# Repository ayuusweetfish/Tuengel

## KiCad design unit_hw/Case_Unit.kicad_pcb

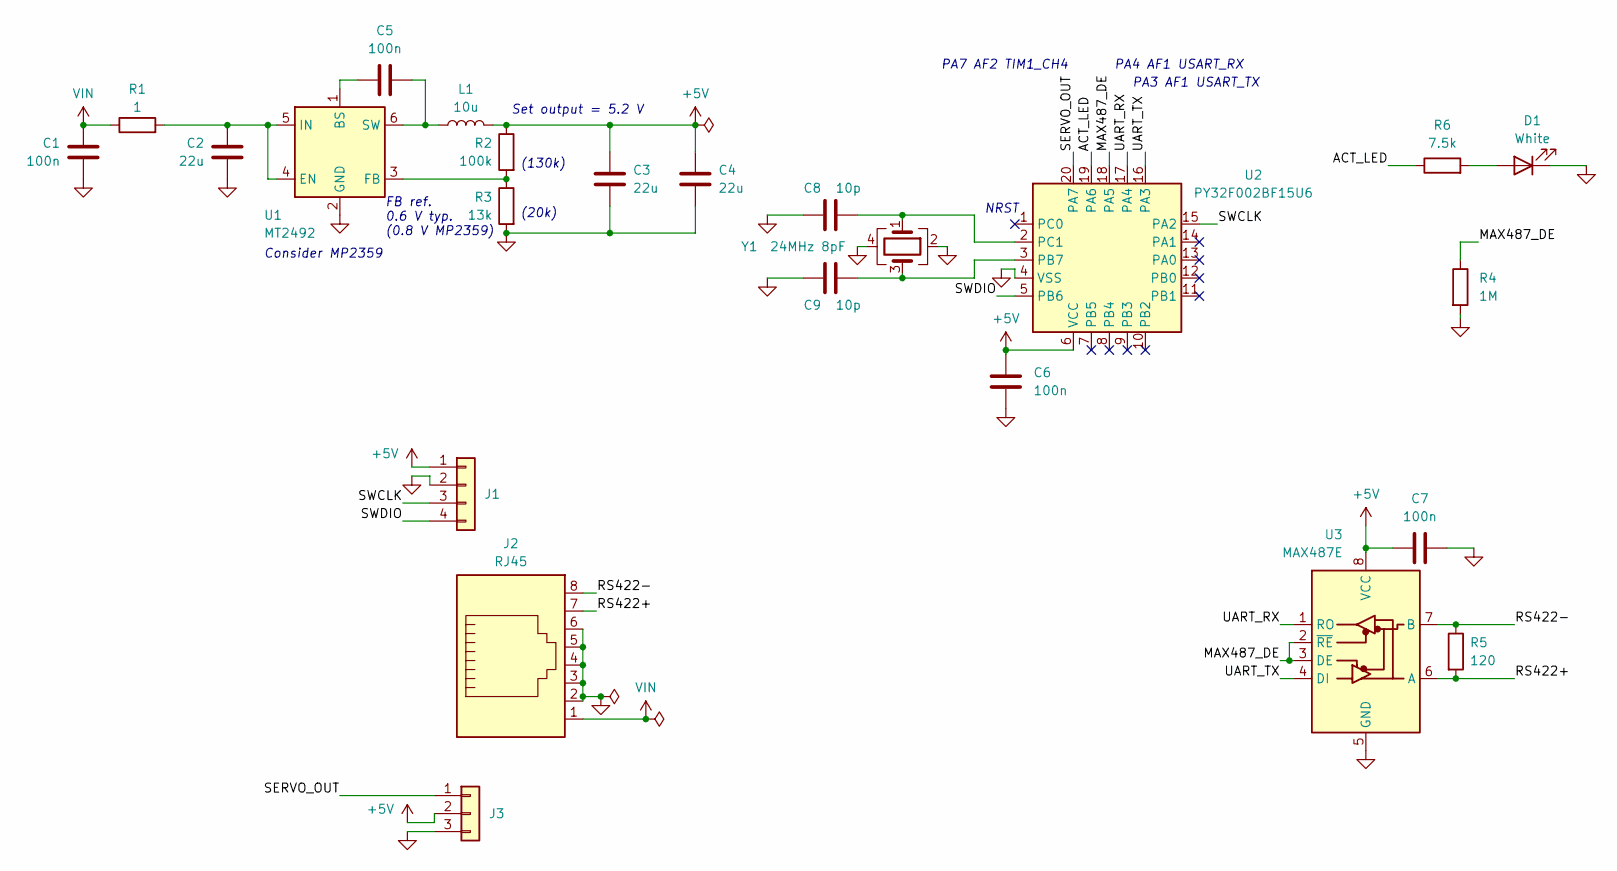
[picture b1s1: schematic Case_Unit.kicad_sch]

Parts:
C1, C5, C6, C7: 100n; C_0402_1005Metric
C2, C3, C4: 22u; C_0603_1608Metric
C8, C9: 10p; C_0402_1005Metric
D1: White; LED_0603_1608Metric
J1: Conn_01x04; TestPoints_1x04_P2.0
J2: RJ45; RJ45_OST_PJ012-8P8CX_Vertical
J3: Conn_01x03; PinHeader_1x03_P2.54mm_Vertical
L1: 10u; L_Changjiang_FNR5030S
R1: 1; R_0402_1005Metric
R2: 100k; R_0402_1005Metric
R3: 13k; R_0402_1005Metric
R4: 1M; R_0402_1005Metric
R5: 120; R_0402_1005Metric
R6: 7.5k; R_0402_1005Metric
U1: MT2492; SOT-23-6; Manufacturer_Part_Number MT2492
U2: PY32F002BF15U6; QFN-20-1EP_3x3mm_P0.4mm_EP1.65x1.65mm
U3: MAX487E; SOIC-8_3.9x4.9mm_P1.27mm
Y1: 24MHz 8pF; Crystal_SMD_2016-4Pin_2.0x1.6mm

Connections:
+5V: C3.1, C4.1, C6.1, C7.1, J1.1, J3.2, L1.2, R2.1, U2.6 (VCC), U3.8 (VCC)
/ACT_LED: R6.1, U2.19 (PA6)
/MAX487_DE: R4.1, U2.18 (PA5), U3.2 (~RE), U3.3 (DE)
/RS422+: J2.7, R5.2, U3.6 (A)
/RS422-: J2.8, R5.1, U3.7 (B)
/SERVO_OUT: J3.1, U2.20 (PA7)
/SWCLK: J1.3, U2.15 (PA2)
/SWDIO: J1.4, U2.5 (PB6)
/UART_RX: U2.17 (PA4), U3.1 (RO)
/UART_TX: U2.16 (PA3), U3.4 (DI)
GND: C1.2, C2.2, C3.2, C4.2, C6.2, C7.2, C8.1, C9.1, D1.1 (K), J1.2, J2.2, J2.3, J2.4, J2.5, J2.6, J3.3, R3.2, R4.2, U1.2 (GND), U2.4 (VSS), U2.21 (PAD), U3.5 (GND), Y1.2, Y1.4
unnamed: D1.2 (A), R6.2
unnamed: C5.1, U1.1 (BS)
unnamed: C2.1, R1.2, U1.4 (EN), U1.5 (IN)
unnamed: R2.2, R3.1, U1.3 (FB)
unnamed: C5.2, L1.1, U1.6 (SW)
unnamed: C9.2, U2.3 (PB7), Y1.3
unnamed: C8.2, U2.2 (PC1), Y1.1
VIN: C1.1, J2.1, R1.1

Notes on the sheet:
PA4 AF1 USART_RX
Consider MP2359
(130k)
NRST
PA3 AF1 USART_TX
FB ref. 0.6 V typ. (0.8 V MP2359)
(20k)
PA7 AF2 TIM1_CH4
Set output = 5.2 V

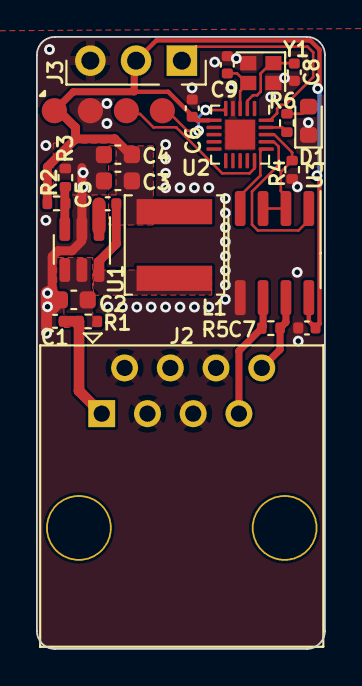
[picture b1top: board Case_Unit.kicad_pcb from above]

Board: 2 copper layers, 16.0 x 34.0 mm, 24 parts (0 on the bottom side), 19 nets.

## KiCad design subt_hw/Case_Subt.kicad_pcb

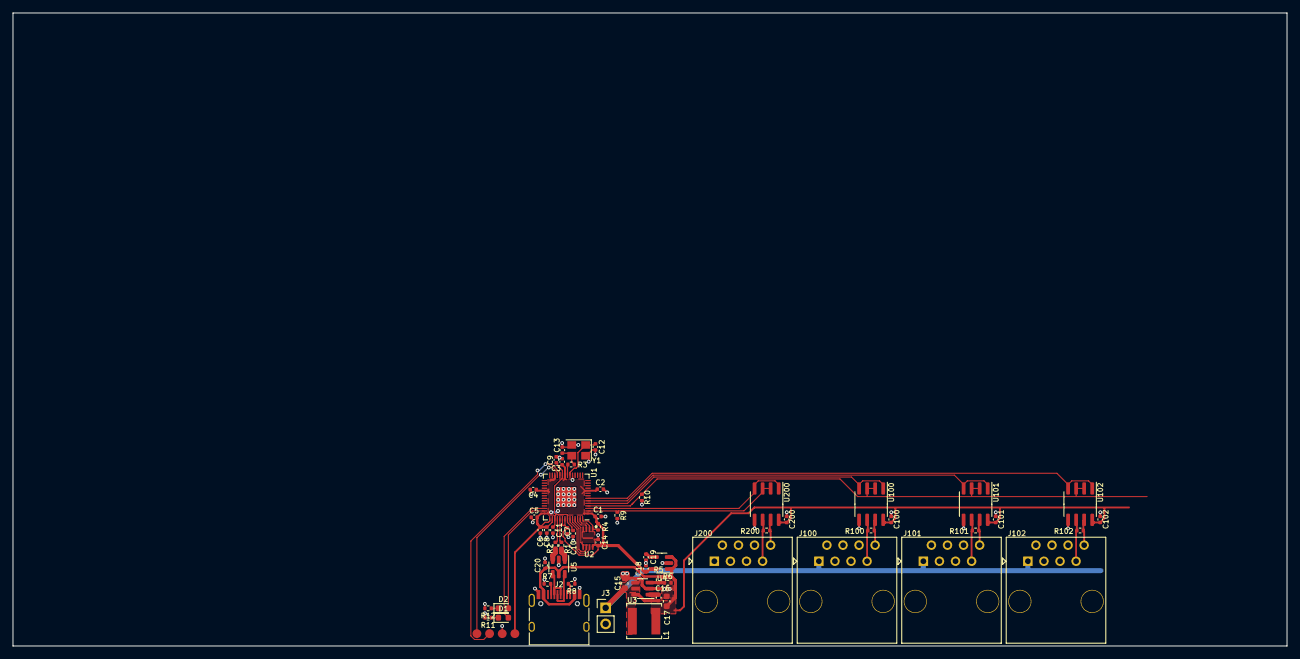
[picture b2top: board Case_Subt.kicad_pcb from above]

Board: 2 copper layers, 201.3 x 100.0 mm, 60 parts (0 on the bottom side), 46 nets.

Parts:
C1, C2, C3, C4, C5, C6, C7, C9, C10, C14, C20, C100, C101, C102, C200: 100n; C_0402_1005Metric
C8, C11: 1u; C_0402_1005Metric
C12, C13: 27p; C_0402_1005Metric
C15, C17: 22u; C_0603_1608Metric
C16: 22n; C_0402_1005Metric
C18: 4.7u; C_0402_1005Metric
C19: 10n; C_0402_1005Metric
D1: Pink; LED_0603_1608Metric
D2: Violet; LED_0603_1608Metric
J1: P2.00 01x04; TestPoints_1x04_P2.0
J2: USB_C_Receptacle_USB2.0_14P; USB_C_Receptacle_HRO_TYPE-C-31-M-12
J3: Conn_01x02; PinHeader_1x02_P2.54mm_Vertical
J100, J101, J102, J200: RJ45; RJ45_OST_PJ012-8P8CX_Vertical
L1: 10u; L_Changjiang_FNR5030S
R1, R2: 22; R_0402_1005Metric
R3: 1k TBD; R_0402_1005Metric
R4, R5: 100k; R_0402_1005Metric
R6: 22k; R_0402_1005Metric
R7, R8: 5.1k; R_0402_1005Metric
R9, R10: 1M; R_0402_1005Metric
R11, R12: 7.5k; R_0402_1005Metric
R100, R101, R102, R200: 120; R_0402_1005Metric
U1: RP2040; QFN-56-1EP_7x7mm_P0.4mm_EP3.2x3.2mm
U2: W25Q16JVUXIQ; SON50P300X200X60-9N
U3: MT2492; SOT-23-6
U4: SPX3819M5-L-3-3; SOT-23-5
U5: USBLC6-2SC6; SOT-23-6
U100, U101, U102, U200: MAX487E; SOIC-8_3.9x4.9mm_P1.27mm
Y1: 12MHz; Crystal_SMD_3225-4Pin_3.2x2.5mm

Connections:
+3V3: C1.1, C2.1, C3.1, C4.1, C5.1, C6.1, C7.1, C8.1, C14.1, C18.1, J1.1, R4.2, U1.1 (IOVDD), U1.10 (IOVDD), U1.22 (IOVDD), U1.26 (RUN), U1.33 (IOVDD), U1.42 (IOVDD), U1.43 (ADC_AVDD), U1.44 (VREG_IN), U1.48 (USB_VDD), U1.49 (IOVDD), U2.8 (VCC), U4.5 (OUT)
+5V: C17.1, C20.1, C100.1, C101.1, C102.1, C200.1, J2.A4 (VBUS), J2.A9 (VBUS), J2.B4 (VBUS), J2.B9 (VBUS), L1.2, R5.1, U4.1 (IN), U4.3 (EN), U5.5 (VBUS), U100.8 (VCC), U101.8 (VCC), U102.8 (VCC), U200.8 (VCC)
/ACT1: D1.2 (A), U1.40 (GPIO28_ADC2)
/ACT2: D2.2 (A), U1.41 (GPIO29_ADC3)
/DATA_00: U1.5 (GPIO3), U100.1 (RO), U100.4 (DI)
/DATA_01: U1.6 (GPIO4), U101.1 (RO), U101.4 (DI)
/DATA_02: U1.7 (GPIO5), U102.1 (RO), U102.4 (DI)
/DATA_IN: U1.3 (GPIO1), U200.1 (RO), U200.4 (DI)
/DE_ALL: R10.1, U1.4 (GPIO2), U100.2 (~RE), U100.3 (DE), U101.2 (~RE), U101.3 (DE), U102.2 (~RE), U102.3 (DE)
/DE_IN: R9.1, U1.2 (GPIO0), U200.2 (~RE), U200.3 (DE)
/FLASH_CS: R4.1, U1.56 (QSPI_SS), U2.1 (~CS)
/FLASH_D0: U1.53 (QSPI_SD0), U2.5 (DI_(IO0))
/FLASH_D1: U1.55 (QSPI_SD1), U2.2 (DO_(IO1))
/FLASH_D2: U1.54 (QSPI_SD2), U2.3 (~WP_(IO2))
/FLASH_D3: U1.51 (QSPI_SD3), U2.7 (~HOLD_OR_RESET_(IO3))
/FLASH_SCK: U1.52 (QSPI_SCLK), U2.6 (CLK)
/In_Conn/DATA+: J200.7, R200.2, U200.6 (A)
/In_Conn/DATA-: J200.8, R200.1, U200.7 (B)
/Out_00/DATA+: J100.7, R100.2, U100.6 (A)
/Out_00/DATA-: J100.8, R100.1, U100.7 (B)
/Out_01/DATA+: J101.7, R101.2, U101.6 (A)
/Out_01/DATA-: J101.8, R101.1, U101.7 (B)
/Out_02/DATA+: J102.7, R102.2, U102.6 (A)
/Out_02/DATA-: J102.8, R102.1, U102.7 (B)
/SWCLK: J1.3, U1.24 (SWCLK)
/SWDIO: J1.4, U1.25 (SWD)
/USB_D+: R1.1, U5.1 (I/O1)
/USB_D-: R2.1, U5.3 (I/O2)
/USB_RAW_D+: J2.A6 (D+), J2.B6 (D+), U5.6 (I/O1)
/USB_RAW_D-: J2.A7 (D-), J2.B7 (D-), U5.4 (I/O2)
GND: C1.2, C2.2, C3.2, C4.2, C5.2, C6.2, C7.2, C8.2, C9.2, C10.2, C11.2, C12.1, C13.1, C14.2, C15.2, C17.2, C18.2, C19.2, C20.2, C100.2, C101.2, C102.2, C200.2, J1.2, J2.A1 (GND), J2.A12 (GND), J2.B1 (GND), J2.B12 (GND), J3.2, J100.2, J100.3, J100.4, J100.5, J100.6, J101.2, J101.3, J101.4, J101.5, J101.6, J102.2, J102.3, J102.4, J102.5, J102.6, J200.2, J200.3, J200.4, J200.5, J200.6, R6.2, R7.1, R8.1, R9.2, R10.2, R11.2, R12.2, U1.19 (TESTEN), U1.57 (GND), U2.4 (GND), U2.9 (EP), U3.2 (GND), U4.2 (GND), U5.2 (GND), U100.5 (GND), U101.5 (GND), U102.5 (GND), U200.5 (GND), Y1.2, Y1.4
unnamed: C13.2, R3.1, Y1.3
unnamed: D1.1 (K), R11.1
unnamed: D2.1 (K), R12.1
unnamed: J2.A5 (CC1), R7.2
unnamed: J2.B5 (CC2), R8.2
unnamed: R2.2, U1.46 (USB_DM)
unnamed: R1.2, U1.47 (USB_DP)
unnamed: C12.2, U1.20 (XIN), Y1.1
unnamed: R3.2, U1.21 (XOUT)
unnamed: C16.1, U3.1 (BS)
unnamed: R5.2, R6.1, U3.3 (FB)
unnamed: C16.2, L1.1, U3.6 (SW)
unnamed: C19.1, U4.4 (BP)
VCORE: C9.1, C10.1, C11.1, U1.23 (DVDD), U1.45 (VREG_VOUT), U1.50 (DVDD)
VIN: C15.1, J3.1, J100.1, J101.1, J102.1, U3.4 (EN), U3.5 (IN)

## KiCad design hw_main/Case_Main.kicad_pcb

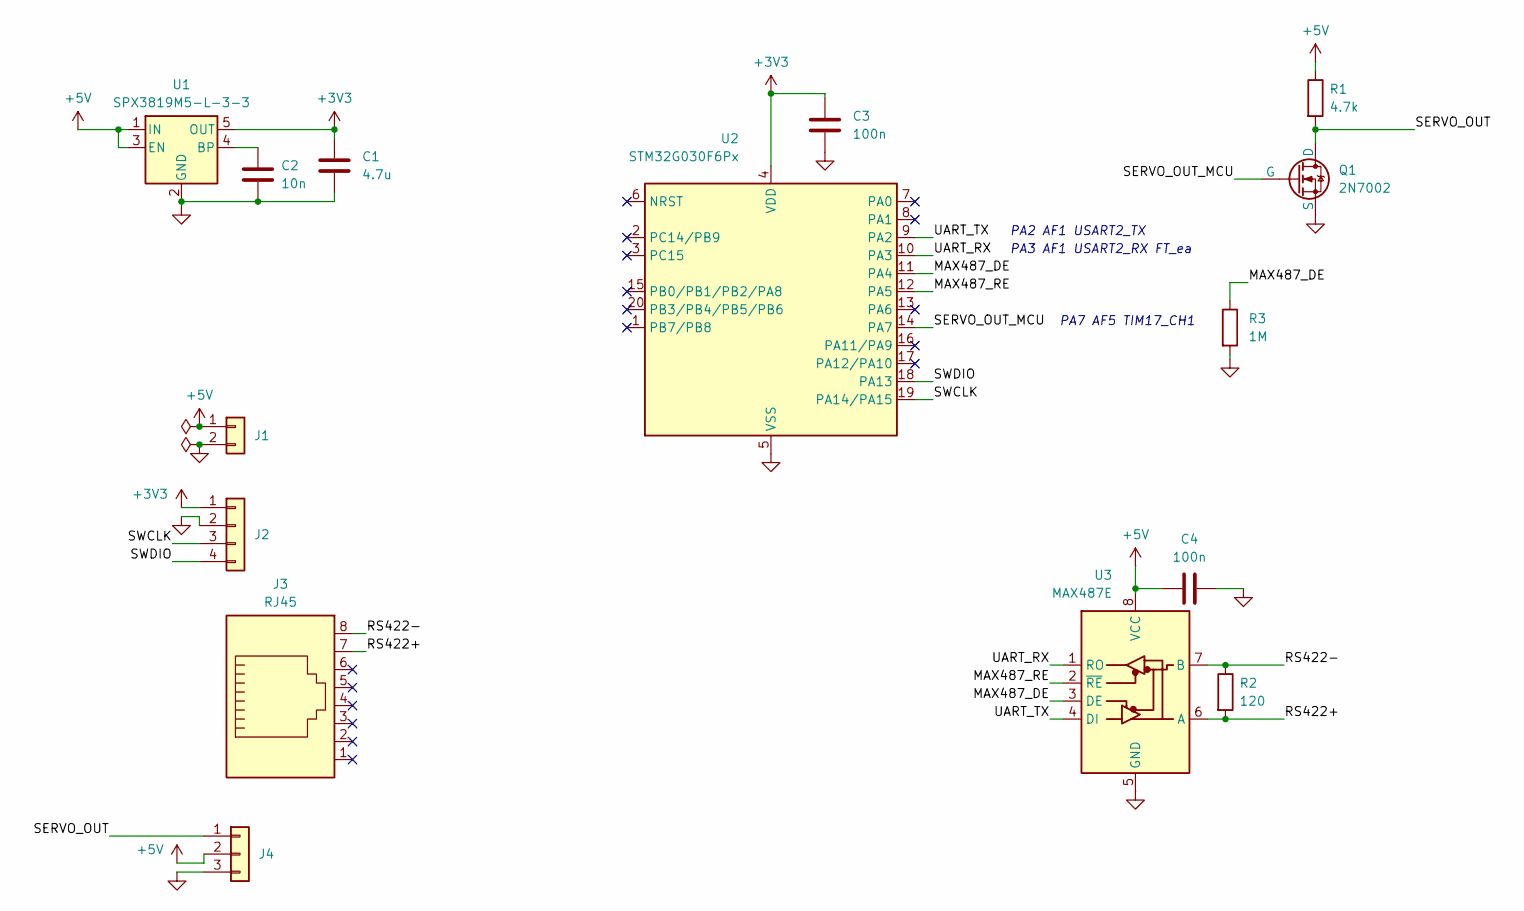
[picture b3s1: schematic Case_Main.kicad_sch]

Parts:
C1: 4.7u; C_0402_1005Metric
C2: 10n; C_0402_1005Metric
C3, C4: 100n; C_0402_1005Metric
J1: Conn_01x02; PinHeader_1x02_P2.54mm_Vertical
J2: Conn_01x04; TestPoints_1x04_P2.0
J3: RJ45; RJ45_OST_PJ012-8P8CX_Vertical
J4: Conn_01x03; PinHeader_1x03_P2.54mm_Vertical
Q1: 2N7002; SOT-23
R1: 4.7k; R_0402_1005Metric
R2: 120; R_0402_1005Metric
R3: 1M; R_0402_1005Metric
U1: SPX3819M5-L-3-3; SOT-23-5
U2: STM32G030F6Px; TSSOP-20_4.4x6.5mm_P0.65mm
U3: MAX487E; SOIC-8_3.9x4.9mm_P1.27mm

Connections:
+3V3: C1.1, C3.1, J2.1, U1.5 (OUT), U2.4 (VDD)
+5V: C4.1, J1.1, J4.2, R1.1, U1.1 (IN), U1.3 (EN), U3.8 (VCC)
/MAX487_DE: R3.1, U2.11 (PA4), U3.3 (DE)
/MAX487_RE: U2.12 (PA5), U3.2 (~RE)
/RS422+: J3.7, R2.2, U3.6 (A)
/RS422-: J3.8, R2.1, U3.7 (B)
/SERVO_OUT: J4.1, Q1.3 (D), R1.2
/SERVO_OUT_MCU: Q1.1 (G), U2.14 (PA7)
/SWCLK: J2.3, U2.19 (PA14/PA15)
/SWDIO: J2.4, U2.18 (PA13)
/UART_RX: U2.10 (PA3), U3.1 (RO)
/UART_TX: U2.9 (PA2), U3.4 (DI)
GND: C1.2, C2.2, C3.2, C4.2, J1.2, J2.2, J4.3, Q1.2 (S), R3.2, U1.2 (GND), U2.5 (VSS), U3.5 (GND)
unnamed: C2.1, U1.4 (BP)

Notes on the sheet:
PA3 AF1 USART2_RX FT_ea
PA2 AF1 USART2_TX
PA7 AF5 TIM17_CH1

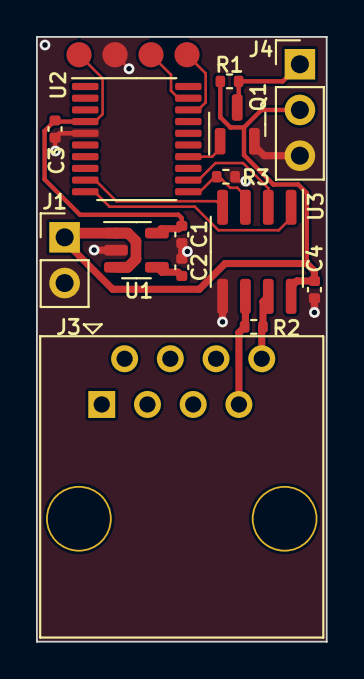
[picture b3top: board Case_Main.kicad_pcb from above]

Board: 2 copper layers, 16.1 x 33.6 mm, 15 parts (0 on the bottom side), 14 nets.

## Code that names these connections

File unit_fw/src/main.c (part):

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  __HAL_RCC_GPIOA_CLK_ENABLE();
  __HAL_RCC_GPIOB_CLK_ENABLE();

  // PA2 - SWCLK, PB6 - SWDIO with correct pull-up/-down upon reset
  // Reference manual v. 1.0 p. 79 (zh) / 77 (en)

  // PA6 - Act LED
  HAL_GPIO_Init(GPIOA, &(GPIO_InitTypeDef){
    .Pin = GPIO_PIN_6,
    .Mode = GPIO_MODE_OUTPUT_PP,
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  HAL_GPIO_WritePin(GPIOA, GPIO_PIN_6, 1);

  // ====== (TIM1) Timer for servo control ======
  // PA7 - TIM1_CH4
  HAL_GPIO_Init(GPIOA, &(GPIO_InitTypeDef){
    .Pin = GPIO_PIN_7,
    .Mode = GPIO_MODE_AF_PP,
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  HAL_TIM_PWM_Start(&tim1, TIM_CHANNEL_4);

  // ====== (USART1) Serial communication ======
  // PA3 - USART_TX
  // PA4 - USART_RX
  HAL_GPIO_Init(GPIOA, &(GPIO_InitTypeDef){
    .Pin = GPIO_PIN_3 | GPIO_PIN_4,
    .Mode = GPIO_MODE_AF_PP,
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  };
  HAL_UART_Init(&uart1);

  // PA5 - MAX487 driver enable
  HAL_GPIO_WritePin(GPIOA, GPIO_PIN_5, 0);
  HAL_GPIO_Init(GPIOA, &(GPIO_InitTypeDef){
    .Pin = GPIO_PIN_5,
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  HAL_IncTick();
  uint32_t t = HAL_GetTick();
  bool act_led = (t - rx_timestamp < 1000 ? (t - rx_timestamp < 300) : (t % 4096 < 100));
  GPIOA->BSRR = (GPIO_PIN_6 << (act_led ? 0 : 16));
}

void USART1_IRQHandler()
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
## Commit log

2024-10-12 🎉 Mallet unit, submit for fab (Rev. 1)
2024-10-13 Start subtree schematic
2024-10-13 Rename main -> unit
2024-10-13 Add all 16 ports
2024-10-13 Simplify wiring
2024-10-14 Add servo testrun firmware
2024-10-14 More motor movements
2024-10-14 Remap servo signal to PB1
2024-10-14 Servo signals through timer PWM
2024-10-14 Sine table...?
2024-10-15 🚧 Router board
2024-10-15 🚧 Layout, without the final stretch
2024-10-15 Finish subtree/router board design
2024-10-15 Submit for fab (Rev. 2 subtree)
2024-10-15 Revise unit schematic
2024-10-15 Submit for fab (Rev. 2 unit)
2024-10-16 Update testrun firmware to match board Rev. 1
2024-10-16 Revise unit board (change PY32 model to 002B; add crystal)
2024-10-16 Finish unit redesign; submit for fab (Rev. 2 unit)
2024-10-17 Add serial protocol design documentation
2024-10-17 🎉 Subtree firmware test with Pico SDK 2.0.0
2024-10-17 Add CRC (CCITT/B-CRC-32)
2024-10-17 Switch to CRC-32 (LSB first)
2024-10-17 Correctly receive packets and verify checksums
2024-10-19 Fix serial stuck/missing data when too fast
2024-10-19 Refactor USB serial reception to be more robust
2024-10-19 Implement the first command (Ping)
2024-10-19 Migrate serial comms to libserialport
2024-10-19 Send & receive with checksums
2024-10-19 Auto-checksum MCU TX payload
2024-10-19 Minor refactor
2024-10-20 Add UART PIO program (untested)
2024-10-20 TX/RX with PIO
2024-10-20 Format PIO code
2024-10-20 Receive and process commands through PIO
2024-10-20 TX through USB or UART depending on data source
    🚧 Missing commands (whole packets) with UART?
2024-10-20 Fix communication glitches
2024-10-20 Refactor and fix potential timing issues with half duplex
2024-10-20 Update subtree hardware with actual values in assembly
2024-10-20 Fix flash script; upload to actual board!
2024-10-20 🎉 Unit blinking firmware
2024-10-20 Remove redundant SWD enable
2024-10-20 Drive servo motor with PY32
2024-10-21 Add RS-422 serial communication (🚧 untested)
2024-10-21 Update unit hardware document with actual values in assembly
2024-10-21 Working UART through RS-422 (unit)
2024-10-22 subt: TX/RX at remappable pins
2024-10-22 Signal serial transmission progress with PIO IRQ
2024-10-22 Refactor for clarity
2024-10-22 🎉 Send data to units
2024-10-22 A few debugging aids
2024-10-22 🚧 Trembling communications established between subtree and unit
2024-10-22 Fix downstream-facing port not transmitting
2024-10-22 Correctly sending to switchable downstream ports
2024-10-23 Send response from the unit, receive at subtree
2024-10-23 Increase baud rate to 115.2 kBd
2024-10-23 Shorten waits between transmissions
2024-10-23 unit: Strike on message reception
2024-10-23 unit: Switch to byte-based processing, achieving auto-recovery from errors
2024-10-23 subt: Filter spurious signal noise in PIO UART
2024-10-23 Clean-ups in firmware
2024-10-23 unit: Implement velocity parameter
2024-10-23 unit: Revise activity LED pattern, finalise firmware
2024-10-23 unit: Fix activity LED pattern not indicating received messages
2024-10-24 subt: Process incoming serial messages at L0
2024-10-24 More granular error messages, 🚧 velocity only 0x7A~0xFD possible?
2024-10-24 subt: Return bitmask for Ping command
2024-10-24 subt: Support omitting velocity in serial command
2024-10-24 subt: Flush RX FIFO at downstream-facing ports
2024-10-24 subt: Finalise firmware for now 🎉
2024-10-24 Print sent data & checksum in serial utility
2024-10-24 Eliminate checksum requirement with USB serial RX
2024-10-25 Add TCP-serial relay
2024-10-26 relay: Build libserialport for Windows
2024-10-26 relay: Forward network traffic to serial
2024-10-26 relay: Forward data received from serial to TCP
2024-10-26 relay: Fix Windows build
2024-10-27 relay: Support command line arguments
2024-10-27 relay: Read arguments from file when none is present
2024-10-27 relay: Fix incorrect reallocation
2024-10-27 relay: Debug switch
2024-10-27 relay: Add debug/dump switch and build hash/date
2024-10-28 relay: Enable DTR, prepare for global retry?
2024-10-28 relay: Add auto-loop bat
2024-10-28 relay: Add a filter function before TX
2024-10-28 relay: Delayed transmission
2024-10-28 relay: Translate commands
2024-10-28 relay: Fix incorrect unit address mapping
2024-10-28 relay: Adjust random patterns
2024-10-28 🎉 Finalise firmware release
